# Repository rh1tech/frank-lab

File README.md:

# FRANK Lab

Official page: **[frank.rh1.tech](https://frank.rh1.tech/)** — hub for all FRANK boards and firmware.

Experimental and work-in-progress boards for the [FRANK](https://github.com/rh1tech/frank) hardware emulation platform.

**WARNING: These boards are untested and unreleased. Do NOT order PCBs from this repository.** They may contain errors, incomplete routing, or unverified component footprints. Use at your own risk.

For production-ready boards, see the main [frank](https://github.com/rh1tech/frank) repository.

## Boards in this repository

| Board | Status |
|-------|--------|
| `frank_air` | Work in progress |
| `frank_core2` | Work in progress — pulled back from the released set |
| `frank_pga2` | 1.00 ready for fab, untested — dual PGA2350 (Core2 link), 2-layer, hand-solderable |
| `dino_z80` | Work in progress — pulled back from the released set |
| `xt8086_beta` | Work in progress — pulled back from the released set |
| `frank_next_proto` | Prototype — superseded by FRANK Next, released |

## Released from this repository

These boards have graduated to [rh1tech/frank](https://github.com/rh1tech/frank) and are no
longer maintained here:

| Was | Now |
|-----|-----|
| `frank_next` | [`hardware/frank_next`](https://github.com/rh1tech/frank/tree/master/hardware/frank_next) — the flagship |
| `frank_core2_proto` | [`hardware/frank_core2_proto`](https://github.com/rh1tech/frank/tree/master/hardware/frank_core2_proto) — published as a prototype |
| `frank_core2u` | [`hardware/frank_core2u`](https://github.com/rh1tech/frank/tree/master/hardware/frank_core2u) |
| `oldskoolfrank` | [`hardware/oldskool`](https://github.com/rh1tech/frank/tree/master/hardware/oldskool) |

Each carries its KiCad project, gerbers, fabrication docs, 3D-printable case and an assembly
guide in English and Russian. Board pages with full specifications are on
[frank.rh1.tech](https://frank.rh1.tech/hardware).

## Author

Mikhail Matveev — <xtreme@rh1.tech> — [rh1.tech](https://rh1.tech)

## License

© 2026 Mikhail Matveev, <xtreme@rh1.tech>

GPL v3. See [LICENSE](./LICENSE).

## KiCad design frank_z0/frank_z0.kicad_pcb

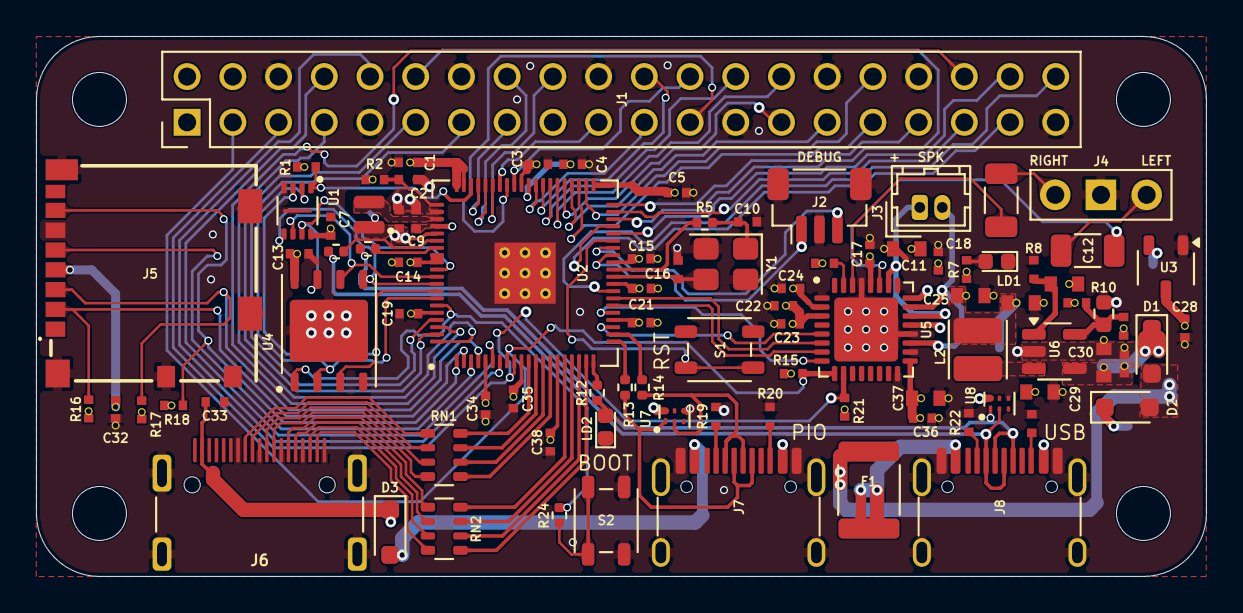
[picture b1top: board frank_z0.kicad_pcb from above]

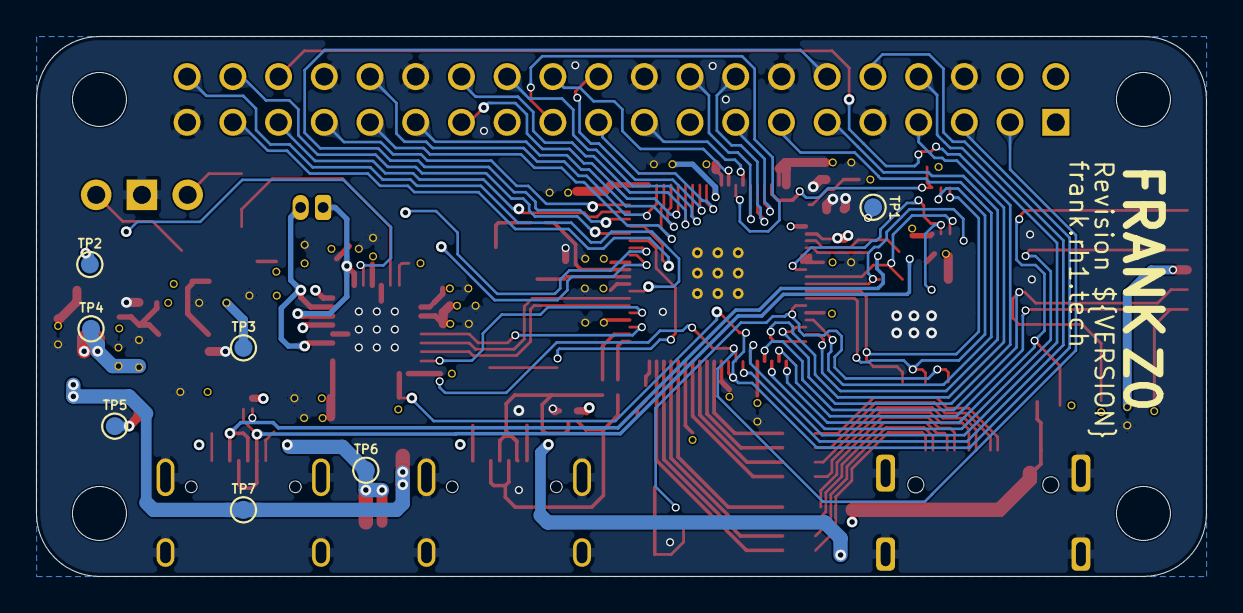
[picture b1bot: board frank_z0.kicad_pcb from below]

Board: 4 copper layers, 65.0 x 30.0 mm, 102 parts (7 on the bottom side), 101 nets.

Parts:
C1, C4, C5, C14, C17, C18, C20, C21, C22, C24, C31, C32, C34, C36: 100n 16V; C_0402_1005Metric_small_pads_Via_GND
C2, C8, C9: 4.7u 10V; C_0402_1005Metric_small_pads
C3, C7, C13, C19, C35, C38: 100n 16V; C_0402_1005Metric_small_pads_Via
C6, C12: 100u 10V; C_1206_3216Metric
C10, C16: 15p 50V; C_0402_1005Metric_small_pads
C11, C25, C26, C29, C30, C37: 10u 25V; C_0603_1608Metric_small_pads_Via_GND
C15: 4.7u 10V; C_0402_1005Metric_small_pads_Via_GND
C23, C28: 1u 25V; C_0402_1005Metric_small_pads_Via_GND
C27: 22p 50V; C_0402_1005Metric_small_pads_Via
C33: 100n 16V; C_0402_1005Metric_small_pads
D1, D2, D3: 1N5819WS; D_SOD-323
F1: 1.5A 24V; Fuse_1812_4532Metric
H1, H2, H3, H4: Mounting Hole (3.0mm); MountingHole_3.0mm
J1: GPIO; PinHeader_2x20_P2.54mm_Vertical
J2: Debug; JST_SH_1x03_P1.00mm_Vertical
J3: Speaker; JST_GH_1x02_P1.25mm
J4: Headphones; PinHeader_1x03_P2.54mm_Vertical
J5: 104031-0811
J6: XDHF-1903-1064; HDMI_Mini_Female
J7, J8: KH-TYPE-C-16P; USB_C_Receptacle
L1: 3.3µH; L_AOTA-B201610_2.0x1.6mm
L2: 2.2u; L_Cenker_CKCS3015
LD1: Green; LED_0603_1608Metric
LD2: Blue; LED_0603_1608Metric
R1, R6, R16, R17, R18: 10K; R_0402_1005Metric_small_pads_Via
R2: 33R; R_0402_1005Metric_small_pads_Via
R3, R4: 27R; R_0402_1005Metric
R5, R24: 1K; R_0402_1005Metric
R7: 1K; R_0402_1005Metric_small_pads_Via
R8: 100K 1%; R_0402_1005Metric_small_pads
R9: 150K 1%; R_0603_1608Metric_small_pads_Via
R10: 22K 1%; R_0603_1608Metric
R11: 100K 1%; R_0402_1005Metric_small_pads_Via
R12: 100R; R_0402_1005Metric
R13, R14: 22R; R_0402_1005Metric
R15, R21: 4.7K; R_0402_1005Metric_small_pads_Via
R19, R20, R22, R23: 5.1K; R_0402_1005Metric_small_pads
RN1, RN2: 270R; R_Array_4x0603
S1: RP Reset; Button_TS-1233_3.3x3.3mm
S2: RP Boot; Button_TS-1233_3.3x3.3mm
TP1: +1V1_A; TestPoint_Pad_D1.0mm
TP2: +1V8; TestPoint_Pad_D1.0mm
TP3: +3V3; TestPoint_Pad_D1.0mm
TP4: VBUS; TestPoint_Pad_D1.0mm
TP5: M_HV_5V; TestPoint_Pad_D1.0mm
TP6: VBUS_USB; TestPoint_Pad_D1.0mm
TP7: VBUS_USB_F; TestPoint_Pad_D1.0mm
U1: APS6404L-3SQR-ZR; PSON50P200X300X50-9N
U2: RP2350B; RP2350-QFN-80_10x10_P0.4mm
U3: XC6206P182MR; XC6206P182MR-G
U4: W25Q128JVPIQ; WSON-8-1EP_6x5mm_P1.27mm_EP3.45x4.35mm
U5: TLV320DAC3100IRHBR
U6: SY8089AAAC; SOT-23-5
U7, U8: TPD4S012DRYR
Y1: 12 MHz; Crystal_SMD_3225-4Pin_3.2x2.5mm

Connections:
+1V1_A: C3.1, C8.1, C15.1, C35.1, L1.1, TP1.1 (1_1), U2.10 (DVDD), U2.32 (DVDD), U2.51 (DVDD), U2.65 (VREG_FB)
+1V8: C22.1, C23.1, TP2.1 (1_1), U3.2 (VOUT), U5.3 (DVDD)
+3V3: C1.1, C4.1, C5.1, C7.1, C9.1, C13.1, C14.1, C17.1, C19.1, C20.1, C21.1, C24.1, C25.1, C26.1, C27.1, C28.1, C29.1, C32.1, C34.1, C36.1, C37.1, C38.1, J1.1, J1.17, J5.4 (VDD), L2.2, R1.1, R2.1, R6.1, R7.1, R11.1, R15.1, R16.1, R17.1, R18.1, R21.1, TP3.1 (1_1), U1.8 (VDD), U2.5 (IOVDD), U2.15 (IOVDD), U2.24 (IOVDD), U2.29 (IOVDD), U2.41 (IOVDD), U2.50 (IOVDD), U2.59 (ADC_AVDD), U2.60 (IOVDD), U2.64 (VREG_VIN), U2.68 (USB_OTP_VDD), U2.69 (QSPI_IOVDD), U2.76 (IOVDD), U3.3 (VIN), U4.8 (VCC), U5.2 (IOVDD), U5.17 (AVDD), U5.28 (HPVDD)
/Audio/SPKM: J3.2, U5.19 (SPKM_1), U5.23 (SPKM_2)
/Audio/SPKP: J3.1, U5.22 (SPKP_1), U5.26 (SPKP_2)
/M0_HD_P13: J1.13, U2.77 (GPIO0)
/M1_HD_P36: J1.36, U2.78 (GPIO1)
/M2_HD_P11: J1.11, U2.79 (GPIO2)
/M3_HD_P7: J1.7, U2.80 (GPIO3)
/M4_SD_DAT0: J5.7 (DAT0), R18.2, U2.1 (GPIO4)
/M5_SD_DAT3: J5.2 (DAT3/CD), R16.2, U2.2 (GPIO5)
/M6_SD_CLK: J5.5 (CLK), U2.3 (GPIO6)
/M7_SD_CMD: J5.3 (CMD), R17.2, U2.4 (GPIO7)
/M8_HD_TX: J1.8, U2.6 (GPIO8)
/M9_HD_RX: J1.10, U2.7 (GPIO9)
/M10_AU_SDA: J1.3, R15.2, U2.8 (GPIO10), U5.9 (SDA)
/M11_AU_SCL: J1.5, R21.2, U2.9 (GPIO11), U5.10 (SCL)
/M12_HV_CLKN: RN1.4 (R4.1), U2.11 (GPIO12)
/M13_HV_CLKP: RN1.3 (R3.1), U2.12 (GPIO13)
/M14_HV_D0N: RN1.2 (R2.1), U2.13 (GPIO14)
/M15_HV_D0P: RN1.1 (R1.1), U2.14 (GPIO15)
/M16_HV_D1N: RN2.4 (R4.1), U2.16 (GPIO16)
/M17_HV_D1P: RN2.3 (R3.1), U2.17 (GPIO17)
/M18_HV_D2N: RN2.2 (R2.1), U2.18 (GPIO18)
/M19_HV_D2P: RN2.1 (R1.1), U2.19 (GPIO19)
/M21_PU_DP: R13.2, U2.21 (GPIO21)
/M22_PU_DM: R14.2, U2.22 (GPIO22)
/M23_AU_DIN: U2.23 (GPIO23), U5.5 (DIN)
/M24_AU_MCLK: U2.25 (GPIO24), U5.8 (MCLK)
/M25_AU_BCLK: U2.26 (GPIO25), U5.7 (BCLK)
/M26_AU_WCLK: U2.27 (GPIO26), U5.6 (WCLK)
/M27_HD_P40: J1.40, U2.28 (GPIO27)
/M28_HD_P38: J1.38, U2.36 (GPIO28)
/M29_HD_P37: J1.37, U2.37 (GPIO29)
/M30_HD_P12: J1.12, U2.38 (GPIO30)
/M31_HD_P35: J1.35, U2.39 (GPIO31)
/M32_HD_P33: J1.33, U2.40 (GPIO32)
/M33_HD_P32: J1.32, U2.42 (GPIO33)
/M34_HD_P31: J1.31, U2.43 (GPIO34)
/M35_HD_P29: J1.29, U2.44 (GPIO35)
/M36_HD_P27: J1.27, U2.45 (GPIO36)
/M37_HD_P28: J1.28, U2.46 (GPIO37)
/M38_HD_P26: J1.26, U2.47 (GPIO38)
/M39_HD_P22: J1.22, U2.48 (GPIO39)
/M40_HD_P21: J1.21, U2.49 (GPIO40_ADC0)
/M41_HD_P24: J1.24, U2.52 (GPIO41_ADC1)
/M42_HD_P23: J1.23, U2.53 (GPIO42_ADC2)
/M43_HD_P19: J1.19, U2.54 (GPIO43_ADC3)
/M44_HD_P18: J1.18, U2.55 (GPIO44_ADC4)
/M45_HD_P16: J1.16, U2.56 (GPIO45_ADC5)
/M46_HD_P15: J1.15, U2.57 (GPIO46_ADC6)
/M_AU_HPL: C12.1, J4.1
/M_AU_HPR: C6.1, J4.3
/M_USB_DM: J8.5 (DN2), J8.7 (DN1), R3.1, U8.2 (D-_)
/M_USB_DP: J8.6 (DP1), J8.8 (DP2), R4.1, U8.1 (D+)
/Power/FB: C27.2, R10.1, R11.2, U6.5 (FB)
/Power/VBUS_USB_F: D1.2 (A), D2.2 (A), F1.2, TP7.1 (1_1)
/RP2350B/BOOT: R24.2, S2.1, S2.2
/RP2350B/M20_LD_LED: R12.2, U2.20 (GPIO20)
/RP2350B/M47_PR_CS: R1.2, U1.1 (~CE), U2.58 (GPIO47_ADC7)
/RP2350B/QSPI_SCLK: U1.6 (SCLK), U2.71 (QSPI_SCLK), U4.6 (CLK)
/RP2350B/QSPI_SD0: U1.5 (SI/SIO(0)), U2.72 (QSPI_SD0), U4.5 (DI_(IO0))
/RP2350B/QSPI_SD1: U1.2 (SO/SIO(1)), U2.74 (QSPI_SD1), U4.2 (DO_(IO1))
/RP2350B/QSPI_SD2: U1.3 (SIO(2)), U2.73 (QSPI_SD2), U4.3 (~WP_(IO2))
/RP2350B/QSPI_SD3: U1.7 (SIO(3)), U2.70 (QSPI_SD3), U4.7 (~HOLD_OR_/RESET_(IO3))
/RP2350B/QSPI_SS: R24.1, U2.75 (QSPI_SS), U4.1 (~CS)
/RP2350B/RUN: S1.1, S1.2, U2.35 (RUN)
/RP2350B/SWCLK: J2.3, U2.33 (SWCLK)
/RP2350B/SWD: J2.1, U2.34 (SWD)
/RP2350B/VREG_AVDD: C2.1, R2.2, U2.61 (VREG_AVDD)
/RP2350B/VREG_LX: L1.2, U2.63 (VREG_LX)
/RP2350B/XIN: C16.1, U2.30 (XIN), Y1.3
/RP2350B/XOUT: R5.2, U2.31 (XOUT)
/VBUS_USB: F1.1, J8.2 (VBUS), J8.11 (VBUS), TP6.1 (1_1), U8.6 (VBUS)
GND: C1.2, C2.2, C3.2, C4.2, C5.2, C7.2, C8.2, C9.2, C10.2, C11.2, C13.2, C14.2, C15.2, C16.2, C17.2, C18.2, C19.2, C20.2, C21.2, C22.2, C23.2, C24.2, C25.2, C26.2, C28.2, C29.2, C30.2, C31.2, C32.2, C33.2, C34.2, C35.2, C36.2, C37.2, C38.2, J1.6, J1.9, J1.14, J1.20, J1.25, J1.30, J1.34, J1.39, J2.2, J4.2, J5.6 (VSS), J5.SH (SHIELD), J6.1 (G_D2), J6.4 (G_D1), J6.7 (G_D0), J6.10 (G_CLK), J6.13 (G_DDC/CEC), J6.SH (SHIELD4), J7.1 (GND), J7.12 (GND), J7.13 (SHIELD), J8.1 (GND), J8.12 (GND), J8.13 (SHIELD), LD1.1 (K), LD2.1 (K), R8.2, R10.2, R19.1, R20.2, R22.1, R23.2, S1.3, S1.4, S2.3, S2.4, U1.4 (VSS), U1.9 (EXP), U2.62 (VREG_PGND), U2.81 (GND), U3.1 (VSS), U4.4 (GND_1), U4.9 (GND_2), U5.1 (IOVSS), U5.16 (AVSS), U5.18 (DVSS), U5.20 (SPKVSS_1), U5.25 (SPKVSS_2), U5.29 (HPVSS), U5.33 (EP), U6.2 (GND), U7.4 (GND), U8.4 (GND), Y1.2, Y1.4
M_HV_5V: C33.1, D2.1 (K), D3.1 (K), J6.18 (+5V), TP5.1 (1_1)
unnamed: C10.1, R5.1, Y1.1
unnamed: J6.12 (CLKN), RN1.5 (R4.2)
unnamed: J6.11 (CLKP), RN1.6 (R3.2)
unnamed: J6.9 (D0N), RN1.7 (R2.2)
unnamed: J6.8 (D0P), RN1.8 (R1.2)
unnamed: J6.6 (D1N), RN2.5 (R4.2)
unnamed: J6.5 (D1P), RN2.6 (R3.2)
unnamed: J6.3 (D2N), RN2.7 (R2.2)
unnamed: J6.2 (D2P), RN2.8 (R1.2)
unnamed: J7.4 (CC1), R19.2
unnamed: J7.10 (CC2), R20.1
unnamed: J7.5 (DN2), J7.7 (DN1), R14.1, U7.2 (D-_)
unnamed: J7.6 (DP1), J7.8 (DP2), R13.1, U7.1 (D+)
unnamed: J8.4 (CC1), R22.2
unnamed: J8.10 (CC2), R23.1
unnamed: LD1.2 (A), R7.2
unnamed: LD2.2 (A), R12.1
unnamed: R3.2, U2.66 (USB_DM)
unnamed: R4.2, U2.67 (USB_DP)
unnamed: C12.2, U5.27 (HPL)
unnamed: C6.2, U5.30 (HPR)
unnamed: R6.2, U5.31 (~RESET)
unnamed: R8.1, R9.2, U6.1 (EN)
unnamed: L2.1, U6.3 (LX)
VBUS: C11.1, C18.1, C30.1, C31.1, D1.1 (K), D3.2 (A), J1.2, J1.4, J7.2 (VBUS), J7.11 (VBUS), R9.1, TP4.1 (1_1), U5.21 (SPKVDD_1), U5.24 (SPKVDD_2), U6.4 (IN), U7.6 (VBUS)

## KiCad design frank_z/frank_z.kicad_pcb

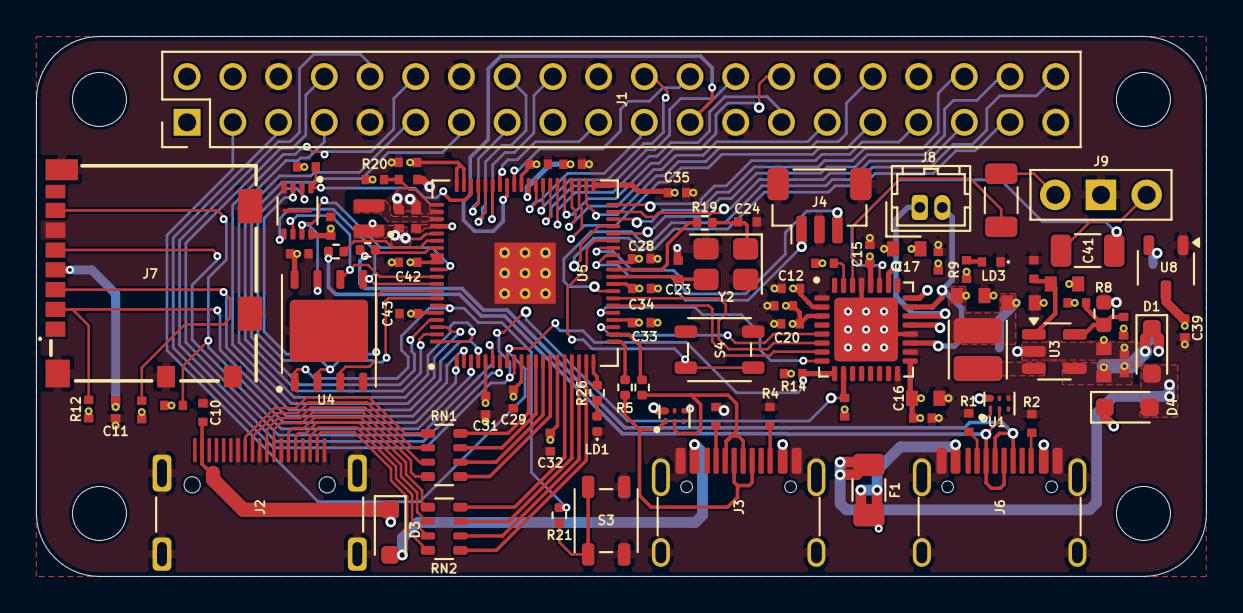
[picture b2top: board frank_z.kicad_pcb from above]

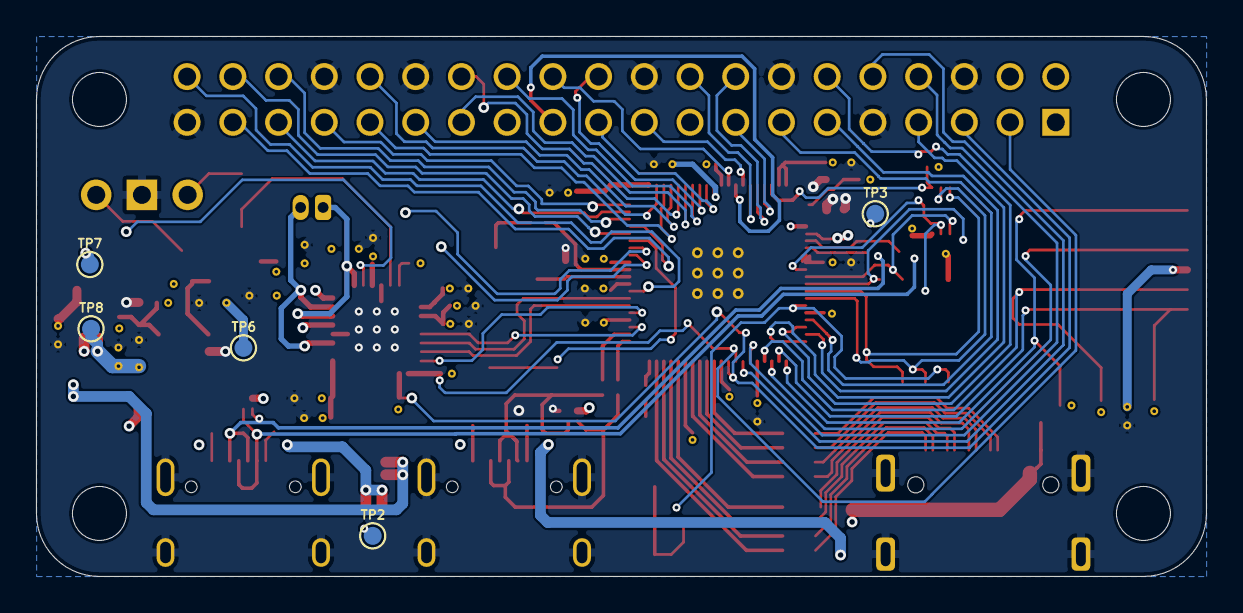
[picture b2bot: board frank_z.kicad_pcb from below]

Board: 4 copper layers, 65.0 x 30.0 mm, 99 parts (5 on the bottom side), 101 nets.

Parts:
C2, C5, C6, C16, C17: 10u 16V; C_0603_1608Metric_small_pads_Via_GND
C4, C11, C12, C13, C15, C18, C19, C31, C33, C34, C35, C36, C37, C42: 100n 16V; C_0402_1005Metric_small_pads_Via_GND
C7: 22p 50V; C_0402_1005Metric_small_pads_Via
C10: 100n 16V; C_0402_1005Metric_small_pads
C20, C39: 1u 16V; C_0402_1005Metric_small_pads_Via_GND
C21, C26, C29, C30, C32, C43: 100n 16V; C_0402_1005Metric_small_pads_Via
C22, C25, C27: 4.7u 10V; C_0402_1005Metric_small_pads
C23, C24: 15p 50V; C_0402_1005Metric_small_pads
C28: 4.7u 10V; C_0402_1005Metric_small_pads_Via_GND
C40, C41: 100u 10V; C_1206_3216Metric
D1, D3, D4: 1N5819WS; D_SOD-323
F1: 1.5A 6V; Fuse_1206_3216Metric
H1, H2, H3, H4: Mounting Hole (3.0mm); MountingHole_3.0mm
J1: GPIO; PinHeader_2x20_P2.54mm_Vertical
J2: HDMI-201; HDMI_Mini_Female
J3, J6: USB4215-03-A; USB_C_Receptacle
J4: Debug; JST_SH_1x03_P1.00mm_Vertical
J7: 104031-0811
J8: Speaker; JST_GH_1x02_P1.25mm
J9: Headphones; PinHeader_1x03_P2.54mm_Vertical
L1: 2.2u; L_Cenker_CKCS3015
L2: 3.3µH; L_AOTA-B201610_2.0x1.6mm
LD1: Blue; LED_0402_1005Metric
LD3: Green; LED_0402_1005Metric_small_pads
R1, R2, R3, R4: 5.1K; R_0402_1005Metric_small_pads
R5, R6: 22R; R_0402_1005Metric
R7: 100K 1%; R_0402_1005Metric_small_pads_Via
R8: 22K 1%; R_0603_1608Metric
R9: 1K; R_0402_1005Metric_small_pads_Via
R10, R11, R12, R15, R23: 10K; R_0402_1005Metric_small_pads_Via
R13, R14: 4.7K; R_0402_1005Metric_small_pads_Via
R16: 150K 1%; R_0603_1608Metric_small_pads_Via
R17: 100K 1%; R_0402_1005Metric_small_pads
R19, R21: 1K; R_0402_1005Metric
R20: 33R; R_0402_1005Metric_small_pads_Via
R24, R25: 27R; R_0402_1005Metric
R26: 100R; R_0402_1005Metric
RN1, RN2: 270R; R_Array_4x0603
S3: RP Boot; Button_TS-1233_3.3x3.3mm
S4: RP Reset; Button_TS-1233_3.3x3.3mm
TP2: VBUS_USB; TestPoint_Pad_D1.0mm
TP3: +1V1_A; TestPoint_Pad_D1.0mm
TP6: +3V3; TestPoint_Pad_D1.0mm
TP7: +1V8; TestPoint_Pad_D1.0mm
TP8: VBUS; TestPoint_Pad_D1.0mm
U1, U2: TPD4S012DRYR
U3: SY8089AAAC; SOT-23-5
U4: W25Q128JVPIQ; WSON-8-1EP_6x5mm_P1.27mm_EP3.45x4.35mm
U5: RP2350B; RP2350-QFN-80_10x10_P0.4mm
U6: APS6404L-3SQR-ZR; PSON50P200X300X50-9N
U7: TLV320DAC3100IRHBR
U8: XC6206P182MR-G
Y2: 12 MHz; Crystal_SMD_3225-4Pin_3.2x2.5mm

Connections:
+1V1_A: C25.1, C28.1, C29.1, C30.1, L2.1, TP3.1 (1_1), U5.10 (DVDD), U5.32 (DVDD), U5.51 (DVDD), U5.65 (VREG_FB)
+1V8: C13.1, C20.1, TP7.1 (1_1), U7.3 (DVDD), U8.2 (VOUT)
+3V3: C5.1, C6.1, C7.1, C11.1, C12.1, C15.1, C16.1, C18.1, C21.1, C22.1, C26.1, C31.1, C32.1, C33.1, C34.1, C35.1, C36.1, C37.1, C39.1, C42.1, C43.1, J1.1, J1.17, J7.4 (VDD), L1.2, R7.1, R9.1, R10.1, R11.1, R12.1, R13.1, R14.1, R15.1, R20.1, R23.1, TP6.1 (1_1), U4.8 (VCC), U5.5 (IOVDD), U5.15 (IOVDD), U5.24 (IOVDD), U5.29 (IOVDD), U5.41 (IOVDD), U5.50 (IOVDD), U5.59 (ADC_AVDD), U5.60 (IOVDD), U5.64 (VREG_VIN), U5.68 (USB_OTP_VDD), U5.69 (QSPI_IOVDD), U5.76 (IOVDD), U6.8 (VDD), U7.2 (IOVDD), U7.17 (AVDD), U7.28 (HPVDD), U8.3 (VIN)
/Audio/SPKM: J8.2, U7.19 (SPKM_1), U7.23 (SPKM_2)
/Audio/SPKP: J8.1, U7.22 (SPKP_1), U7.26 (SPKP_2)
/M0_HD_P13: J1.13, U5.77 (GPIO0)
/M1_HD_P12: J1.12, U5.78 (GPIO1)
/M2_HD_P11: J1.11, U5.79 (GPIO2)
/M3_HD_P7: J1.7, U5.80 (GPIO3)
/M4_SD_DAT0: J7.7 (DAT0), R10.2, U5.1 (GPIO4)
/M5_SD_DAT3: J7.2 (DAT3/CD), R12.2, U5.2 (GPIO5)
/M6_SD_CLK: J7.5 (CLK), U5.3 (GPIO6)
/M7_SD_CMD: J7.3 (CMD), R11.2, U5.4 (GPIO7)
/M8_HD_TX: J1.8, U5.6 (GPIO8)
/M9_HD_RX: J1.10, U5.7 (GPIO9)
/M10_AU_SDA: J1.3, R14.2, U5.8 (GPIO10), U7.9 (SDA)
/M11_AU_SCL: J1.5, R13.2, U5.9 (GPIO11), U7.10 (SCL)
/M12_HV_CLKN: RN1.4 (R4.1), U5.11 (GPIO12)
/M13_HV_CLKP: RN1.3 (R3.1), U5.12 (GPIO13)
/M14_HV_D0N: RN1.2 (R2.1), U5.13 (GPIO14)
/M15_HV_D0P: RN1.1 (R1.1), U5.14 (GPIO15)
/M16_HV_D1N: RN2.4 (R4.1), U5.16 (GPIO16)
/M17_HV_D1P: RN2.3 (R3.1), U5.17 (GPIO17)
/M18_HV_D2N: RN2.2 (R2.1), U5.18 (GPIO18)
/M19_HV_D2P: RN2.1 (R1.1), U5.19 (GPIO19)
/M21_PU_DP: R5.2, U5.21 (GPIO21)
/M22_PU_DM: R6.2, U5.22 (GPIO22)
/M23_AU_DIN: U5.23 (GPIO23), U7.5 (DIN)
/M24_AU_MCLK: U5.25 (GPIO24), U7.8 (MCLK)
/M25_AU_BCLK: U5.26 (GPIO25), U7.7 (BCLK)
/M26_AU_WCLK: U5.27 (GPIO26), U7.6 (WCLK)
/M27_HD_P40: J1.40, U5.28 (GPIO27)
/M28_HD_P38: J1.38, U5.36 (GPIO28)
/M29_HD_P37: J1.37, U5.37 (GPIO29)
/M30_HD_P36: J1.36, U5.38 (GPIO30)
/M31_HD_P35: J1.35, U5.39 (GPIO31)
/M32_HD_P33: J1.33, U5.40 (GPIO32)
/M33_HD_P32: J1.32, U5.42 (GPIO33)
/M34_HD_P31: J1.31, U5.43 (GPIO34)
/M35_HD_P29: J1.29, U5.44 (GPIO35)
/M36_HD_P28: J1.28, U5.45 (GPIO36)
/M37_HD_P27: J1.27, U5.46 (GPIO37)
/M38_HD_P26: J1.26, U5.47 (GPIO38)
/M39_HD_P22: J1.22, U5.48 (GPIO39)
/M40_HD_P21: J1.21, U5.49 (GPIO40_ADC0)
/M41_HD_P24: J1.24, U5.52 (GPIO41_ADC1)
/M42_HD_P23: J1.23, U5.53 (GPIO42_ADC2)
/M43_HD_P19: J1.19, U5.54 (GPIO43_ADC3)
/M44_HD_P18: J1.18, U5.55 (GPIO44_ADC4)
/M45_HD_P16: J1.16, U5.56 (GPIO45_ADC5)
/M46_HD_P15: J1.15, U5.57 (GPIO46_ADC6)
/M_AU_HPL: C41.1, J9.1
/M_AU_HPR: C40.1, J9.3
/M_USB_DM: J6.5 (DN2), J6.7 (DN1), R25.1, U1.2 (D-_)
/M_USB_DP: J6.6 (DP1), J6.8 (DP2), R24.1, U1.1 (D+)
/Power/FB: C7.2, R7.2, R8.1, U3.5 (FB)
/Power/VBUS_USB_F: D1.2 (A), D4.2 (A), F1.2
/RP2350B/BOOT: R21.2, S3.1, S3.2
/RP2350B/M20_LD_LED: R26.2, U5.20 (GPIO20)
/RP2350B/M47_PR_CS: R23.2, U5.58 (GPIO47_ADC7), U6.1 (~CE)
/RP2350B/QSPI_SCLK: U4.6 (CLK), U5.71 (QSPI_SCLK), U6.6 (SCLK)
/RP2350B/QSPI_SD0: U4.5 (DI_(IO0)), U5.72 (QSPI_SD0), U6.5 (SI/SIO(0))
/RP2350B/QSPI_SD1: U4.2 (DO_(IO1)), U5.74 (QSPI_SD1), U6.2 (SO/SIO(1))
/RP2350B/QSPI_SD2: U4.3 (~WP_(IO2)), U5.73 (QSPI_SD2), U6.3 (SIO(2))
/RP2350B/QSPI_SD3: U4.7 (~HOLD_OR_/RESET_(IO3)), U5.70 (QSPI_SD3), U6.7 (SIO(3))
/RP2350B/QSPI_SS: R21.1, U4.1 (~CS), U5.75 (QSPI_SS)
/RP2350B/RUN: S4.1, S4.2, U5.35 (RUN)
/RP2350B/SWCLK: J4.3, U5.33 (SWCLK)
/RP2350B/SWD: J4.1, U5.34 (SWD)
/RP2350B/VREG_AVDD: C27.1, R20.2, U5.61 (VREG_AVDD)
/RP2350B/VREG_LX: L2.2, U5.63 (VREG_LX)
/RP2350B/XIN: C23.1, U5.30 (XIN), Y2.3
/RP2350B/XOUT: R19.2, U5.31 (XOUT)
/VBUS_USB: F1.1, J6.2 (VBUS), J6.11 (VBUS), TP2.1 (1_1), U1.6 (VBUS)
GND: C2.2, C4.2, C5.2, C6.2, C10.2, C11.2, C12.2, C13.2, C15.2, C16.2, C17.2, C18.2, C19.2, C20.2, C21.2, C22.2, C23.2, C24.2, C25.2, C26.2, C27.2, C28.2, C29.2, C30.2, C31.2, C32.2, C33.2, C34.2, C35.2, C36.2, C37.2, C39.2, C42.2, C43.2, J1.6, J1.9, J1.14, J1.20, J1.25, J1.30, J1.34, J1.39, J2.1 (G_D2), J2.4 (G_D1), J2.7 (G_D0), J2.10 (G_CLK), J2.13 (G_DDC/CEC), J2.SH (SHIELD4), J3.1 (GND), J3.12 (GND), J3.13 (SHIELD), J4.2, J6.1 (GND), J6.12 (GND), J6.13 (SHIELD), J7.6 (VSS), J7.SH (SHIELD), J9.2, LD1.1 (K), LD3.1 (K), R1.1, R2.2, R3.1, R4.2, R8.2, R17.2, S3.3, S3.4, S4.3, S4.4, U1.4 (GND), U2.4 (GND), U3.2 (GND), U4.4 (GND_1), U4.9 (GND_2), U5.62 (VREG_PGND), U5.81 (GND), U6.4 (VSS), U6.9 (EXP), U7.1 (IOVSS), U7.16 (AVSS), U7.18 (DVSS), U7.20 (SPKVSS_1), U7.25 (SPKVSS_2), U7.29 (HPVSS), U7.33 (EP), U8.1 (VSS), Y2.2, Y2.4
M_HV_5V: C10.1, D3.1 (K), D4.1 (K), J2.18 (+5V)
unnamed: C24.1, R19.1, Y2.1
unnamed: J2.12 (CLKN), RN1.5 (R4.2)
unnamed: J2.11 (CLKP), RN1.6 (R3.2)
unnamed: J2.9 (D0N), RN1.7 (R2.2)
unnamed: J2.8 (D0P), RN1.8 (R1.2)
unnamed: J2.6 (D1N), RN2.5 (R4.2)
unnamed: J2.5 (D1P), RN2.6 (R3.2)
unnamed: J2.3 (D2N), RN2.7 (R2.2)
unnamed: J2.2 (D2P), RN2.8 (R1.2)
unnamed: J3.4 (CC1), R3.2
unnamed: J3.10 (CC2), R4.1
unnamed: J3.5 (DN2), J3.7 (DN1), R6.1, U2.2 (D-_)
unnamed: J3.6 (DP1), J3.8 (DP2), R5.1, U2.1 (D+)
unnamed: J6.4 (CC1), R1.2
unnamed: J6.10 (CC2), R2.1
unnamed: LD1.2 (A), R26.1
unnamed: LD3.2 (A), R9.2
unnamed: R16.2, R17.1, U3.1 (EN)
unnamed: L1.1, U3.3 (LX)
unnamed: R25.2, U5.66 (USB_DM)
unnamed: R24.2, U5.67 (USB_DP)
unnamed: C41.2, U7.27 (HPL)
unnamed: C40.2, U7.30 (HPR)
unnamed: R15.2, U7.31 (~RESET)
VBUS: C2.1, C4.1, C17.1, C19.1, D1.1 (K), D3.2 (A), J1.2, J1.4, J3.2 (VBUS), J3.11 (VBUS), R16.1, TP8.1 (1_1), U2.6 (VBUS), U3.4 (IN), U7.21 (SPKVDD_1), U7.24 (SPKVDD_2)
